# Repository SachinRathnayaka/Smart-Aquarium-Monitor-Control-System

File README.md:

<div align="center">

# 🐠 SRAqua Guard
### Ultimate Smart Aquarium Monitor & Automation System

*Real-time water telemetry · Intelligent automation · Voice control · Cross-platform monitoring*

---

**Author:** [Sachin Rathnayaka](https://github.com/SachinRathnayaka) &nbsp;·&nbsp; **Repo:** [Smart-Aquarium-Monitor-Control-System](https://github.com/SachinRathnayaka/Smart-Aquarium-Monitor-Control-System) &nbsp;·&nbsp; **Live Demo:** [Web Dashboard](https://sachinrathnayaka.github.io/Smart-Aquarium-Monitor-Control-System/)

</div>

---

## 📖 Table of Contents

- [Project Status](#-project-status)
- [Project Overview](#-project-overview)
- [Visual Showcase](#-visual-showcase)
- [Key Features](#-key-features)
- [System Architecture](#-system-architecture)
- [Repository Structure](#-repository-structure)
- [Getting Started](#-getting-started)
  - [Prerequisites](#prerequisites)
  - [1 · Firmware (ESP32)](#1--firmware-esp32)
  - [2 · Web Dashboard](#2--web-dashboard)
  - [3 · Android App](#3--android-app)
  - [4 · Windows Desktop App](#4--windows-desktop-app)
  - [Pre-built Binaries](#pre-built-binaries)
- [Firebase Configuration](#-firebase-configuration)
- [Voice Commands](#-voice-commands)
- [Sensor Calibration](#-sensor-calibration)
- [Troubleshooting](#-troubleshooting)
- [Electrical Safety](#-electrical-safety)
- [Hardware & PCB](#-hardware--pcb)
- [Bill of Materials](#-bill-of-materials-summary)
- [Roadmap](#️-roadmap)
- [Contributing](#-contributing)
- [Licensing](#-licensing)

---

## 🚧 Project Status

**Status: Active Development**

SRAqua Guard is an actively developed open-source hardware and software project. Features, firmware behaviour, PCB revisions, and application interfaces may change between releases. The project is functional and has been tested with real hardware — see the Visual Showcase for screenshots. Always refer to the latest `main` branch for the most current state.

| Component | Status |
|---|---|
| ESP32 Firmware | ✅ Functional |
| Web Dashboard | ✅ Functional |
| Android App | ✅ Functional |
| Windows Desktop App | ✅ Functional |
| KiCad PCB (Hardware) | ✅ Complete |
| Documentation | ✅ Complete |

---

## 🌊 Project Overview

**SRAqua Guard** is a fully open-source, advanced IoT aquarium monitoring and automation system that transforms any aquarium into an intelligently managed ecosystem. The system is built around an **ESP32 microcontroller** with a custom **KiCad PCB**, pushing real-time sensor telemetry to **Firebase Realtime Database**, and surfaced through three client platforms — a browser-based web dashboard, an Android mobile app, and a Windows desktop app.

The firmware is engineered with a **fully non-blocking `millis()` architecture**, a **DS3231 RTC** as the sole time source (ensuring offline-safe automation), and intelligent fallback behavior: the system continues sensing, controlling, and displaying locally even without Wi-Fi. When battery voltage drops below a threshold, the ESP32 enters a **5-minute deep sleep cycle** to preserve power.

> [!NOTE]
> This project includes **240 V AC mains wiring** for the water heater relay. All high-voltage sections must be handled by a qualified person. Use appropriate insulation, cable sleeving, and maintain required creepage clearances at all times.

---

## 🖼️ Visual Showcase

### Web Dashboard

| Overview | Firebase Setup | Theme Settings |
|:---:|:---:|:---:|
|  |  |  |

| 21-Day Sensor Analytics | 21-Day Feed Analytics | Auto Feeder Scheduler |
|:---:|:---:|:---:|
|  |  |  |

| Live Voice Assistant | Voice Commands List | Alerts & History |
|:---:|:---:|:---:|
|  |  |  |

---

### Android Mobile App

| Firebase Setup | Telemetry & Sensors | Header Navigation | Command Center | App Icon |
|:---:|:---:|:---:|:---:|:---:|
|  |  |  |  |  |

---

### Windows Desktop App

| Main Dashboard | Firebase Setup | Theme Settings | Command Center | Desktop Icon |
|:---:|:---:|:---:|:---:|:---:|
|  |  |  |  |  |

---

### Custom KiCad PCB — 3D Renders

**Standard Renders**

| Top | Bottom | Front | Back | Left | Right |
|:---:|:---:|:---:|:---:|:---:|:---:|
|  |  |  |  |  |  |

**Raytraced Renders**

| Top | Bottom | Front | Back | Left | Right |
|:---:|:---:|:---:|:---:|:---:|:---:|
|  |  |  |  |  |  |

---

## ✨ Key Features

### 🔬 Water Quality Telemetry
- **Temperature** via DS18B20 OneWire sensor — with DS18B20 power-on sentinel (85 °C) rejection
- **pH** via analog sensor module — linear calibration with configurable slope/offset
- **TDS (Total Dissolved Solids)** via analog sensor — temperature-compensated formula
- **Turbidity** via analog sensor — quadratic NTU conversion with 20-point Simple Moving Average (SMA) and degradation trend prediction (days to next maintenance)
- Sensor readings every **2 seconds** in non-blocking loop

### ⚙️ Intelligent Automation
| Condition | Automatic Response |
|---|---|
| Temperature > 29 °C | Cooling fan ON |
| Temperature < 25 °C | Water heater ON (with 30-min hard safety cutoff) |
| Turbidity > 35 NTU or TDS > 500 ppm | Submersible pump ON |
| Turbidity > 70 NTU | Alarm buzzer ON |
| pH outside 6.3–8.3 | Alarm buzzer ON |
| TDS > 1200 ppm | Auto water-change sequence (8-min max, 1-hr cooldown) |
| Pump running 2 h+ with high turbidity | Filter-change alert pushed to Firebase + LCD |
| Temperature sensor fault (OOR / 85 °C sentinel) | Heater hard-disabled, buzzer triggered |
| Battery-only inferred (voltage < 11.2 V, no charge trend) | All loads OFF → 5-min deep sleep cycle |

### 💡 ARGB Lighting Day-Cycle (RTC-driven)
| Time | Lighting |
|---|---|
| 06:00 – 09:59 | Sunrise — dim orange / warm yellow |
| 10:00 – 17:59 | Daytime — bright white / light blue |
| 18:00 – 05:59 | Night — calm breathing blue/purple (non-blocking animation) |

### 🎙️ Voice Assistant
- **8 core command groups** (Status · Feed · Pump · Heater · Fan · Lights · Buzzer · Mode) plus Demo Mode test commands, via the **Web Speech API** — no cloud API key required
- Live transcription displayed in the dashboard header (auto-stops after 15 s of silence, or 5 s after the last detected word)
- Voice TTS feedback: browser speaks alert summaries aloud

### 📅 Auto Fish Feeder
- Servo-based feeder FSM (4-state: Idle → Extend → Hold → Return)
- Unlimited scheduled feeds — configurable time, day(s) of week, specific date, and portion count
- Manual one-click feed button on web/local dashboard
- Daily feed counter persisted in browser `localStorage`

### 🔋 Power Telemetry
- 12 V battery voltage via resistor-divider (×4 ratio) on GPIO 33
- Battery percentage from 9.0 V (0%) to 12.6 V (100%)
- Charging inference via 10-point voltage trend (>50 mV rise = charging)
- Solar charging input terminal on PCB (J15)

### 🖥️ Web Dashboard

👉 **[🚀 Try Live Web Dashboard Here](https://sachinrathnayaka.github.io/Smart-Aquarium-Monitor-Control-System/)** *(Fully functional Demo Mode available — no hardware required!)*

- Pure single-file HTML5/CSS3/JavaScript — **zero build step, zero dependencies to install**
- Firebase Realtime Database v10.8.0 SDK — real-time bidirectional sync
- **4 built-in themes:** Ocean · Cyber · Emerald · Sunset + custom hex color picker
- **Demo Mode** — fully functional without any hardware (simulated sensor data)
- 21-day historical analytics charts (Temperature, pH, TDS, Turbidity, Feed count) via Chart.js
- ARGB hex color picker — picks and syncs live `light_color` to Firebase
- RTC time sync — pushes browser clock to ESP32 via Firebase (`/commands/rtc_sync`)
- Alerts & notification history (last 50 events)

---

## 🏗️ System Architecture

```
┌─────────────────────────────────────────────────────────────────────┐
│                        ESP32 (Firmware)                             │
│                                                                     │
│  Sensors ──► readAllSensors() ──► evaluateAutomation()              │
│  DS18B20 · pH · TDS · Turbidity · Battery                           │
│                    │                                                │
│         millis() non-blocking loop (no delay())                     │
│                    │                                                │
│  ┌─────────────────┼─────────────────────────┐                     │
│  │ DS3231 RTC      │ FastLED ARGB   Servo     │                     │
│  │ (offline time)  │ (day cycle)    (feeder)  │                     │
│  └─────────────────┼─────────────────────────┘                     │
│                    │                                                │
│         pushFirebase() every 5 s  ◄──►  Firebase RTDB              │
│         streamCallback()          ◄──►  /controls + /commands       │
│         Local WebServer (port 80) → in-network dashboard            │
└─────────────────────────────────────────────────────────────────────┘
                              │
                  Firebase Realtime Database
                  /devices/aquaSense/
                  ├── sensors/
                  ├── status/
                  ├── controls/
                  ├── commands/
                  └── alerts/
                              │
          ┌───────────────────┼───────────────────┐
          │                   │                   │
   Web Dashboard        Android App         Windows App
   (index.html)     (WebView wrapper)    (Electron shell)
   Any browser      com.wrscn.sraquaguard  com.wrscn.sraquaguard
```

### ESP32 GPIO Pin Map

| Pin | Signal | Direction |
|-----|--------|-----------|
| GPIO 34 | pH Sensor (Analog) | Input |
| GPIO 35 | TDS Sensor (Analog) | Input |
| GPIO 32 | Turbidity Sensor (Analog) | Input |
| GPIO 25 | DS18B20 Temperature (1-Wire) | Input |
| GPIO 33 | BMS / Battery Voltage (Analog) | Input |
| GPIO 26 | Cooling Fan Relay | Output |
| GPIO 27 | Submersible Pump Relay | Output |
| GPIO 17 | Water Heater Relay ⚠️ 240 V | Output |
| GPIO 23 | Fish Feeder Servo (PWM) | Output |
| GPIO 16 | ARGB LED Strip (WS2812B) | Output |
| GPIO 13 | Alarm Buzzer | Output |
| GPIO 21 | I²C SDA (LCD + RTC) | I²C |
| GPIO 22 | I²C SCL (LCD + RTC) | I²C |
| GPIO 4 | Wi-Fi / Firebase Status LED | Output |

### Arduino Libraries Required

| Library | Purpose | Install via |
|---------|---------|-------------|
| `Firebase ESP Client` by mobizt | Firebase RTDB | Arduino Library Manager |
| `LiquidCrystal I2C` | 16×2 LCD display | Arduino Library Manager |
| `DallasTemperature` | DS18B20 sensor | Arduino Library Manager |
| `OneWire` | 1-Wire bus | Arduino Library Manager |
| `RTClib` | DS3231 RTC | Arduino Library Manager |
| `FastLED` | WS2812B ARGB LEDs | Arduino Library Manager |
| `ESP32Servo` | Servo motor control | Arduino Library Manager |

---

## 📁 Repository Structure

```
Smart-Aquarium-Monitor-Control-System/
│
├── 📁 Firmware/
│   └── ESP32/
│       └── IoT_Based_Smart_Aquarium_Monitor__Control_System_ESP32/
│           ├── IoT_Based_Smart_Aquarium_Monitor__Control_System_ESP32.ino
│           │   # Main ESP32 firmware — non-blocking millis() architecture,
│           │   # offline-safe automation, DS3231 RTC, Firebase RTDB streaming,
│           │   # ARGB day cycle, feeder FSM, battery telemetry, deep sleep
│           └── secrets.example.h
│               # Credential template — copy to secrets.h, fill in values,
│               # add secrets.h to .gitignore (never commit real credentials)
│
├── 📁 Web_Dashboard/
│   ├── index.html          # Single-file dashboard — no build step required
│   └── assets/
│       └── logo.png
│
├── 📁 Android_App/          # Android Studio project (com.wrscn.sraquaguard)
│   ├── app/
│   │   ├── build.gradle    # compileSdk 35, minSdk 23 (Android 6.0+), versionName 1.0
│   │   └── src/main/
│   │       ├── AndroidManifest.xml
│   │       ├── assets/
│   │       │   ├── index.html      # Bundled web dashboard
│   │       │   └── assets/logo.png
│   │       ├── java/com/wrscn/sraquaguard/
│   │       │   └── MainActivity.java  # WebView with immersive fullscreen
│   │       └── res/
│   │           ├── drawable/sraqua_logo.png
│   │           ├── mipmap-*/       # Launcher icons (all densities)
│   │           └── values/
│   │               ├── colors.xml
│   │               └── styles.xml  # Theme.SRAquaGuard (dark slate)
│   └── README.md
│
├── 📁 Windows_App/          # Electron desktop application
│   ├── main.js             # BrowserWindow 1280×800, contextIsolation: true
│   ├── index.html          # Dashboard file loaded by Electron
│   ├── package.json        # electron + electron-builder, NSIS target
│   ├── package-lock.json
│   └── assets/
│       ├── logo.ico        # Windows app icon
│       └── logo.png
│
├── 📁 Hardware/             # KiCad 10.0.3 PCB project
│   ├── *.kicad_pcb         # PCB layout
│   ├── *.kicad_sch         # Schematic
│   ├── *.kicad_pro         # Project file
│   ├── 3D_Models/
│   │   ├── 3D_Standard/    # 6 standard 3D renders (Top/Bottom/Sides)
│   │   └── 3D_Raytraced/   # 6 raytraced 3D renders (Top/Bottom/Sides)
│   ├── Gerber_Files/       # Full Gerber set (F_Cu, B_Cu, Masks, Silkscreen,
│   │   ├── *.gbr           #   Edge Cuts, Drill files) + zipped Gerber bundle
│   │   └── Gerber_ZIP/
│   └── DIY_Etching_PDFs/   # PDFs for DIY toner-transfer / UV etching
│       ├── Copper_Layers/  # Top + Bottom copper (normal + mirrored)
│       ├── Silkscreen_Layers/
│       └── Assembly_Drawings/
│
├── 📁 Docs/
│   ├── Bill_of_Materials.md          # 41 line items · 74 total components
│   ├── Components_List_BOM.csv       # Machine-readable BOM
│   ├── Schematic_Diagram.pdf         # Full schematic PDF export
│   └── PCB_Artwork_Etching_Layout.pdf
│
├── 📁 Images/               # All screenshots and renders used in this README
│   ├── 3D_PCB_Isometric.png
│   ├── ESP32_Pin_Pitch_Dimensions.png
│   ├── Web_Dashboard_Screenshots/    # 9 screenshots
│   ├── Mobile_App_Screenshots/       # 5 screenshots
│   └── Desktop_App_Screenshots/      # 5 screenshots
│
└── README.md
```

---

## 🚀 Getting Started

### Prerequisites

| Requirement | Details |
|---|---|
| Arduino IDE ≥ 2.x **or** PlatformIO | For flashing the ESP32 firmware |
| ESP32 Arduino Core | Board package for ESP32 (add `https://raw.githubusercontent.com/espressif/arduino-esp32/gh-pages/package_esp32_index.json` to board manager) |
| Firebase project | Free Spark plan is sufficient — Realtime Database enabled |
| Any modern browser | Chrome recommended for Voice Control (Web Speech API) |
| Android Studio (optional) | To build the `.apk` from source |
| Node.js ≥ 18 (optional) | To run/build the Windows Electron app from source |

---

### 1 · Firmware (ESP32)

#### Step 1 — Install Libraries

Open **Arduino IDE → Tools → Manage Libraries** and install each of the following:

```
Firebase ESP Client    (by mobizt)
LiquidCrystal I2C
DallasTemperature
OneWire
RTClib
FastLED
ESP32Servo
```

#### Step 2 — Configure Credentials (secrets.h pattern)

To avoid accidentally committing credentials to a public repository, use the recommended `secrets.h` approach:

**2a.** Copy the provided template:
```
Firmware/ESP32/.../secrets.example.h  →  copy as  secrets.h
```

**2b.** Open `secrets.h` and fill in your values:
```cpp
// secrets.h — DO NOT commit this file
#pragma once

// Wi-Fi
#define WIFI_SSID     "YOUR_WIFI_SSID"
#define WIFI_PASSWORD "YOUR_WIFI_PASSWORD"

// Firebase
#define API_KEY       "YOUR_FIREBASE_API_KEY"
#define DATABASE_URL  "YOUR_FIREBASE_DATABASE_URL"
#define USER_EMAIL    "YOUR_FIREBASE_USER_EMAIL"
#define USER_PASSWORD "YOUR_FIREBASE_USER_PASSWORD"
```

**2c.** Add `secrets.h` to your `.gitignore` so it is never tracked:
```
# .gitignore
secrets.h
```

The main `.ino` file already contains `#include "secrets.h"` and uses these defines — **do not paste real credentials directly into the `.ino` file.**

> [!WARNING]
> **Never commit real credentials to a public repository.** The `secrets.example.h` template uses intentionally non-functional placeholder strings. Always work from `secrets.h` (git-ignored) in your local copy.

> [!NOTE]
> **Firebase API Key vs secret credentials:** The Firebase Web API Key (found in Project Settings) is a *project identifier* — it is not a secret by itself, as it is embedded in every web client. What must be protected are your **Firebase Auth user email and password** (the device account). Firebase Database Rules (see the Firebase Configuration section) are your primary security boundary — ensure they are correctly configured before going live.

#### Step 3 — Sensor Calibration (optional)

The firmware ships with **Dummy Data switches** that generate realistic random values for dry testing without any sensors connected:

```cpp
bool DUMMY_PH        = false;   // set true for dry test
bool DUMMY_TDS       = false;
bool DUMMY_TURBIDITY = false;
bool DUMMY_TEMP      = false;
bool DUMMY_BATTERY   = false;
```

For a real deployment, calibrate your pH probe and update:

```cpp
float PH_SLOPE  = -5.70f;   // Adjust after 2-point calibration
float PH_OFFSET = 21.34f;
```

#### Step 4 — Flash

Select **Board: `ESP32 Dev Module`**, choose the correct COM port, then click **Upload**.

---

### 2 · Web Dashboard

The dashboard is a **single self-contained HTML file** with no build step.

**Option A — Open locally in browser**
```
Open Web_Dashboard/index.html directly in Chrome or Edge
```

**Option B — Host on GitHub Pages**
1. Copy `Web_Dashboard/index.html` and `Web_Dashboard/assets/` to the root of a GitHub Pages branch.
2. Enable GitHub Pages in your repository settings.
3. Share the `https://<username>.github.io/<repo>/` URL.

**Connecting to Firebase**

When the dashboard loads, a setup modal appears. Enter your Firebase project credentials:

| Field | Where to find it |
|---|---|
| **API Key** | Firebase Console → Project Settings → General |
| **Database URL** | Firebase Console → Realtime Database → Data tab |
| **User Email** | Firebase Console → Authentication → Users |
| **User Password** | The password for that Firebase Auth user |

Click **Connect Firebase** to go live, or **Enter Demo Mode** to explore with simulated data — no hardware needed.

---

### 3 · Android App

**Build from source (Android Studio)**

1. Open the `Android_App/` folder in **Android Studio**.
2. Allow Gradle to sync (compileSdk 35, minSdk 23 — Android 6.0+).
3. Build the APK:

```bash
./gradlew assembleDebug
# Output: Android_App/app/build/outputs/apk/debug/app-debug.apk
```

Or use **Build → Build App Bundle(s)/APK(s) → Build APK(s)** from the menu.

The app loads `index.html` bundled in `app/src/main/assets/` via a hardware-accelerated WebView with immersive fullscreen mode. Firebase credentials are configured through the in-app setup modal — no separate `google-services.json` is needed.

> [!NOTE]
> The web dashboard inside the APK includes its own Firebase setup flow. Simply enter your Firebase credentials the first time you launch the app, and they are persisted in the WebView's `localStorage`.

---

### 4 · Windows Desktop App

**Run from source**

```bash
cd Windows_App
npm install
npm start
```

**Build an installable `.exe`**

```bash
npm run build
# Output: Windows_App/dist/SRAqua Guard Setup x.x.x.exe  (NSIS installer)
```

The Electron window opens at **1280 × 800** (minimum 1000 × 650) and loads `index.html`. Node integration is disabled (`nodeIntegration: false`, `contextIsolation: true`) for security.

---

### Pre-built Binaries

Pre-compiled binaries are published through the **GitHub Releases** page. Check the Releases tab for the latest available versions:

| Platform | File | Notes |
|---|---|---|
| Android | `SRAqua_Guard_v1.0.apk` | Sideload — enable "Install from unknown sources" in device settings |
| Windows | `SRAqua Guard Setup 1.0.0.exe` | NSIS installer — run and follow on-screen prompts |

👉 **[View GitHub Releases](https://github.com/SachinRathnayaka/Smart-Aquarium-Monitor-Control-System/releases)**

> [!NOTE]
> If no release is listed yet, build from source using the instructions above — it only takes a few minutes.

---

## 🔥 Firebase Configuration

### Database Path Structure

All device data lives under a single root path:

```
/devices/aquaSense/
├── sensors/            ← pushed by ESP32 every 5 s
│   ├── temperature_c
│   ├── ph_value / ph_voltage
│   ├── tds_ppm / tds_voltage
│   ├── turbidity_ntu / turbidity_sma
│   ├── predicted_days_to_maintenance
│   ├── battery_voltage / battery_percent
│   ├── charging_inferred
│   ├── dummy_ph / dummy_tds / dummy_turbidity / dummy_temp / dummy_battery
│   └── timestamp
├── status/             ← pushed by ESP32 every 5 s
│   ├── manual_mode / fan / pump / heater / buzzer
│   ├── water_change_active / filter_change_required
│   ├── wifi_connected / firebase_ready / battery_only_mode
├── controls/           ← written by dashboard, read by ESP32 stream
│   ├── manual_mode / manual_fan / manual_pump
│   ├── manual_heater / manual_buzzer
│   ├── manual_light / light_color
│   └── feed_now
├── commands/           ← one-shot voice hooks (auto-reset after each push)
│   ├── voice_feed
│   ├── voice_pump
│   └── rtc_sync
└── alerts/
    └── filter_change_required_at
```

### Recommended Security Rules

The rules below apply **least-privilege** access: only authenticated users can read or write device data. No unauthenticated access is permitted at any path.

```json
{
  "rules": {
    ".read":  false,
    ".write": false,
    "devices": {
      "aquaSense": {
        "sensors":  { ".read": "auth != null", ".write": "auth != null" },
        "status":   { ".read": "auth != null", ".write": "auth != null" },
        "controls": { ".read": "auth != null", ".write": "auth != null" },
        "commands": { ".read": "auth != null", ".write": "auth != null" },
        "alerts":   { ".read": "auth != null", ".write": "auth != null" }
      }
    }
  }
}
```

> [!IMPORTANT]
> **Never use `".read": true, ".write": true`** (open rules) — this exposes your device data to anyone on the internet. The root-level `false` defaults above ensure that any path not explicitly listed is denied by default. The firmware authenticates using the dedicated Firebase Auth device account configured in `secrets.h`.

> [!NOTE]
> For a single-owner deployment, the `auth != null` check is sufficient since only your device account and your own dashboard sessions are authenticated. For multi-user or team setups, consider tightening rules further using `auth.uid` matching against an allow-list stored in the database.

> [!TIP]
> **Future enhancement — role-based rules:** In an ideal setup, write permissions would be further restricted by path role: `sensors/` and `status/` would be write-restricted to the ESP32 device account only, while `controls/` and `commands/` would be writable by dashboard users. This can be implemented by storing your ESP32's Firebase Auth UID in the database and matching against it in rules. For a personal single-device deployment the current rules are adequate.

### Authentication Setup

1. In Firebase Console → **Authentication → Sign-in method**, enable **Email/Password**.
2. Under **Authentication → Users**, click **Add user** and create a dedicated device account.
3. Use those credentials in the firmware's `USER_EMAIL` and `USER_PASSWORD` defines.

---

## 🎙️ Voice Commands

Voice control uses the browser's built-in **Web Speech API** (no API key required). Click the **Voice Control** button in the dashboard header, then speak any of the following commands:

| Voice Command | Alternatives | Action |
|---|---|---|
| **"Tell Status"** | "Tank Status", "How is the water" | Reads the current sensor values via TTS and reports whether the aquarium conditions are healthy or critical |
| **"Feed"** | — | Triggers fish feeder immediately — sends `voice_feed` to Firebase |
| **"Pump on"** | "Turn on pump" | Enables manual mode and turns pump ON — sends `voice_pump` to Firebase |
| **"Pump off"** | "Turn off pump" | Enables manual mode and turns pump OFF |
| **"Heater on"** | "Turn on heater" | Enables manual mode and turns heater ON |
| **"Heater off"** | "Turn off heater" | Enables manual mode and turns heater OFF |
| **"Fan on"** | "Turn on fan" | Enables manual mode and turns cooling fan ON |
| **"Fan off"** | "Turn off fan" | Enables manual mode and turns cooling fan OFF |
| **"Lights on"** | "Light on", "Turn on lights" | Turns ARGB tank lights ON |
| **"Lights off"** | "Light off", "Turn off lights" | Turns ARGB tank lights OFF |
| **"Buzzer on"** | "Turn on buzzer" | Manually enables alarm buzzer |
| **"Buzzer off"** | "Turn off buzzer" | Manually disables alarm buzzer |
| **"Auto Mode"** | "Auto" | Switches system to automatic control |
| **"Manual Mode"** | "Manual" | Switches system to manual control |
| **"Test Alert"** | — | Simulates a critical alert (Demo Mode) |
| **"Fix Alert"** | "Reset Alert" | Restores simulated normal conditions (Demo Mode) |

> [!NOTE]
> Voice control requires a browser that supports the Web Speech API (Chrome and Edge recommended). Microphone permission must be granted. The recognition session auto-stops after **15 seconds** of silence, or **5 seconds** after the last detected word. Web Speech API support and behaviour may vary by browser version and operating system — Chrome on desktop provides the most consistent experience.

---

## 🧪 Sensor Calibration

The firmware ships with **Dummy Data mode** for all sensors — ideal for testing the dashboard and Firebase integration without any physical hardware connected. Set the relevant flag to `true` in the firmware:

```cpp
bool DUMMY_PH        = false;   // set true to generate simulated pH readings
bool DUMMY_TDS       = false;
bool DUMMY_TURBIDITY = false;
bool DUMMY_TEMP      = false;
bool DUMMY_BATTERY   = false;
```

### pH Calibration (2-point method)

Perform a standard 2-point calibration using pH 4.0 and pH 7.0 buffer solutions:

1. Dip the probe in **pH 7.0** buffer → note the raw ADC voltage reading from the serial monitor.
2. Dip the probe in **pH 4.0** buffer → note the second ADC voltage reading.
3. Calculate slope and offset from those two readings, then update the firmware:

```cpp
float PH_SLOPE  = -5.70f;   // Volts per pH unit — adjust after calibration
float PH_OFFSET = 21.34f;   // Intercept — adjust after calibration
```

> [!NOTE]
> The default values above (`PH_SLOPE = -5.70`, `PH_OFFSET = 21.34`) are example starting points. Your actual probe will require calibration — results will be inaccurate if you skip this step.

### TDS Calibration

The TDS sensor uses a temperature-compensated formula built into the firmware. For best accuracy, perform the reading in water at a known temperature and compare against a reference TDS meter. Adjust the conversion coefficient in firmware if needed.

### Turbidity Calibration

Turbidity uses a quadratic NTU conversion with a 20-point Simple Moving Average (SMA) for stability. The SMA also drives the degradation trend prediction (days to next filter maintenance). If your sensor module outputs a different voltage curve, update the quadratic coefficients in the firmware.

### Battery Voltage Calibration

The battery voltage is measured via a ×4 resistor divider on GPIO 33. If your resistor values differ slightly, adjust the divider ratio constant in firmware to match your measured real-world voltage.

---

## 🛠️ Troubleshooting

| Symptom | Likely Cause | Fix |
|---|---|---|
| ESP32 won't connect to Wi-Fi | Wrong credentials in `secrets.h` | Double-check `WIFI_SSID` and `WIFI_PASSWORD` — no extra spaces |
| Firebase stream not receiving data | Firebase rules blocking access | Verify security rules and that `USER_EMAIL`/`USER_PASSWORD` match an active Auth user |
| No sensor readings on dashboard | Wiring issue or Dummy Data off | Check GPIO connections against the pin map, or enable Dummy Data mode for testing |
| Temperature always reads 85 °C | DS18B20 power-on sentinel not rejected / wiring fault | Check 1-Wire pull-up resistor (4.7 kΩ on GPIO 25) and sensor wiring |
| pH / TDS / Turbidity readings wildly wrong | Uncalibrated sensor | Perform 2-point calibration — see Sensor Calibration section above |
| Android build fails (Gradle error) | Gradle/SDK mismatch | Run **File → Sync Project with Gradle Files** in Android Studio; ensure SDK 35 is installed |
| Electron app won't start | Missing Node modules | Run `npm install` inside `Windows_App/` before `npm start` |
| Voice commands not recognised | Browser or permission issue | Use Chrome or Edge; grant microphone permission when prompted; ensure Web Speech API is supported on your OS |
| ARGB lights show wrong colour | `light_color` hex not synced | Use the colour picker in the dashboard — it pushes the hex directly to Firebase `/controls/light_color` |
| Heater relay not triggering | Heater hard-disabled due to sensor fault | Check serial monitor for fault messages; verify DS18B20 wiring and that temperature reads correctly |

> [!NOTE]
> For firmware issues, always open the **Arduino IDE Serial Monitor** at **115200 baud** immediately after flashing — the firmware prints detailed startup diagnostics and runtime status every cycle.

---

## ⚡ Electrical Safety

> [!CAUTION]
> **This project involves 240 V AC mains voltage. Incorrect wiring can cause electric shock, fire, or death. Read this section fully before building.**

| Safety Requirement | Details |
|---|---|
| **Qualified person** | All mains-voltage wiring (relay K5, terminals J17/J18) must be connected and tested only by a suitably qualified person |
| **Mains-rated wiring** | Use cable rated ≥ 250 V for all AC sections — correctly sleeved and terminated |
| **Fusing** | Two 5 A / 250 V slow-blow fuses are included in the BOM and PCB layout — always fit them before energising |
| **Enclosure** | House the PCB in an IP-rated enclosure appropriate for the installation environment. Never leave mains terminals exposed |
| **Creepage & clearance** | Maintain the required PCB creepage distances between high-voltage and low-voltage traces — do not bridge them with solder bridges or conductive debris |
| **Low/high voltage separation** | Keep all 240 V AC wiring physically separated from the 5 V / 3.3 V signal wiring at all times |
| **RCD / GFCI protection** | Install an RCD (residual current device) or GFCI on the mains circuit feeding this system — especially important near water |
| **Waterproofing** | The PCB is not waterproof. Protect it from splashes. All sensor probes that enter the aquarium must be rated for submersion |
| **Heater safety cutoff** | The firmware enforces a **30-minute hard cutoff** on the heater relay and disables it on any temperature sensor fault — do not bypass this logic |

**Never power the mains section of the board during firmware development or debugging.** Work with the AC terminals disconnected and use the Dummy Data mode for testing.

---

## 🔩 Hardware & PCB

The custom PCB was designed in **KiCad 10.0.3** as a through-hole friendly layout suitable for DIY etching or professional PCB fabrication.

### PCB Outputs Provided

| Output | Location | Use |
|---|---|---|
| KiCad project files (`.kicad_pcb`, `.kicad_sch`, `.kicad_pro`) | `Hardware/` | Edit in KiCad 10.x |
| Gerber files + drill files | `Hardware/Gerber_Files/` | Send to any PCB fab (JLCPCB, PCBWay, OSH Park…) |
| Zipped Gerber bundle | `Hardware/Gerber_Files/Gerber_ZIP/` | Ready to upload directly to fab ordering page |
| DIY etching PDFs | `Hardware/DIY_Etching_PDFs/` | Toner-transfer / photoresist etching |
| Standard 3D renders (×6) | `Hardware/3D_Models/3D_Standard/` | Documentation / review |
| Raytraced 3D renders (×6) | `Hardware/3D_Models/3D_Raytraced/` | Realistic visual preview |
| Schematic PDF | `Docs/Schematic_Diagram.pdf` | Reference during assembly |

### ESP32 Fit Note

The PCB accepts a standard **ESP32-WROOM-32 / ESP32-DevKitC 38-pin** module mounted on two 1×19 female pin socket rows.

> [!WARNING]
> The board routes **240 V AC mains** through relay K5 (water heater output). Terminals J17 (AC out) and J18 (AC in) must use mains-rated wiring (≥ 250 V rated, properly sleeved). Observe required creepage distances. This section must only be connected and tested by a qualified person.

---

## 📋 Bill of Materials Summary

Full BOM: [`Docs/Bill_of_Materials.md`](Docs/Bill_of_Materials.md) · CSV: [`Docs/Components_List_BOM.csv`](Docs/Components_List_BOM.csv)

**The hardware design uses exclusively through-hole components to support DIY-friendly assembly.**

| Category | Key Parts |
|---|---|
| Microcontroller | ESP32-WROOM-32 / DevKitC (38-pin) |
| Transistors | BC547 NPN (relay drivers) |
| Relays | SANYOU SRD Form-C (5 V coil, 10 A / 250 VAC) |
| Diodes | SR560 Schottky (4×) · 1N4007 rectifier (4×) · RS505 bridge (1×) | 
| Capacitors | 100 nF ceramic (4×) · 470 µF electrolytic (1×) · 1000 µF (3×) · 10 µF (1×) |
| Resistors | 330 Ω – 30 kΩ (various, ¼ W 5%) |
| Fuses | 5 A / 250 V slow-blow, 5×20 mm |
| Power Module | LM2596 / MP1584 DC-DC buck (12 V → 5 V) |
| Connectors | Screw terminals (5.08 mm) + pin headers (2.54 mm) |
| Switch | 6×6 mm tactile push button (Reset/Boot) |

---

## 🗺️ Roadmap

Planned improvements and ideas for future releases. Community contributions towards any of these are very welcome — see [Contributing](#-contributing).

| Feature | Description | Status |
|---|---|---|
| OTA firmware updates | Push firmware updates to the ESP32 wirelessly via Firebase or a local server | Planned |
| Additional sensor support | Water level sensor, dissolved oxygen (DO), CO₂ | Planned |
| Push notifications | Mobile push alerts via Firebase Cloud Messaging when alarms trigger | Planned |
| Advanced automation rules | User-configurable threshold values stored in Firebase (no reflash required) | Planned |
| Extended analytics | Analytics beyond 21 days; CSV export of historical sensor data | Planned |
| Multi-aquarium support | Extend the Firebase path structure to manage multiple tanks from one dashboard | Planned |
| Role-based Firebase security | Per-path UID-restricted rules (ESP32 write-only to `sensors/status/`, dashboard write-only to `controls/commands/`) | Planned |
| Android: native push notifications | Background service for alarm delivery when the app is not in the foreground | Planned |

> [!NOTE]
> This roadmap reflects current intentions and may change. Items marked **Planned** have not been started. If you have ideas or want to contribute to any of these, open an issue to discuss.

---

## 🤝 Contributing

Contributions are warmly welcomed! Whether it's a bug fix, new feature, improved calibration formula, or documentation update — please feel free to open an issue or pull request.

**Guidelines:**

1. **Fork** the repository and create your branch from `main`.
2. Follow the existing code style — especially the non-blocking `millis()` pattern in firmware (no `delay()` in `loop()`).
3. For dashboard changes, test in both **Demo Mode** and **Firebase Mode**.
4. For hardware changes, verify in KiCad 10.x and update the BOM accordingly.
5. **Never commit real Wi-Fi SSIDs, passwords, or Firebase API keys** — always use placeholder strings.
6. Open a **Pull Request** with a clear description of what was changed and why.

**Reporting Issues:**

Please include your ESP32 core version, Arduino IDE version, and relevant serial output when reporting firmware bugs.

---

## 📜 Licensing

This project utilizes a multi-licensing model to cover software, hardware, and documentation appropriately:

- 💻 **Software & Firmware:** Licensed under the [MIT License](LICENSE) (ESP32 Firmware, Web Dashboard, Android & Windows Apps).
- 🛠️ **Hardware Design:** Licensed under the [CERN-OHL-S-2.0](LICENSE-HARDWARE) (KiCad Schematics & PCB Layouts).
- 📄 **Documentation & Media:** Licensed under [CC BY 4.0](LICENSE-DOCS) (Guides, Images, and Diagrams).

Copyright © 2026 Sachin Rathnayaka (WRSCN)

---

<div align="center">

Made with ❤️ by **[Sachin Rathnayaka (WRSCN)](https://github.com/SachinRathnayaka)**

⭐ If this project helped you, please consider giving it a star on GitHub!

</div>

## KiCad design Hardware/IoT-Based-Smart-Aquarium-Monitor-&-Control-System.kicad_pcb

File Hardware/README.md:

# Hardware Architecture & KiCad PCB Design

This directory contains the KiCad 10.0 schematic and PCB layout files for the SRAqua Guard Smart Aquarium Automation System.

## License
All hardware schematics, PCB designs, and 3D models in this directory are licensed under the **CERN Open Hardware Licence Version 2 - Strongly Reciprocal (CERN-OHL-S-2.0)**.

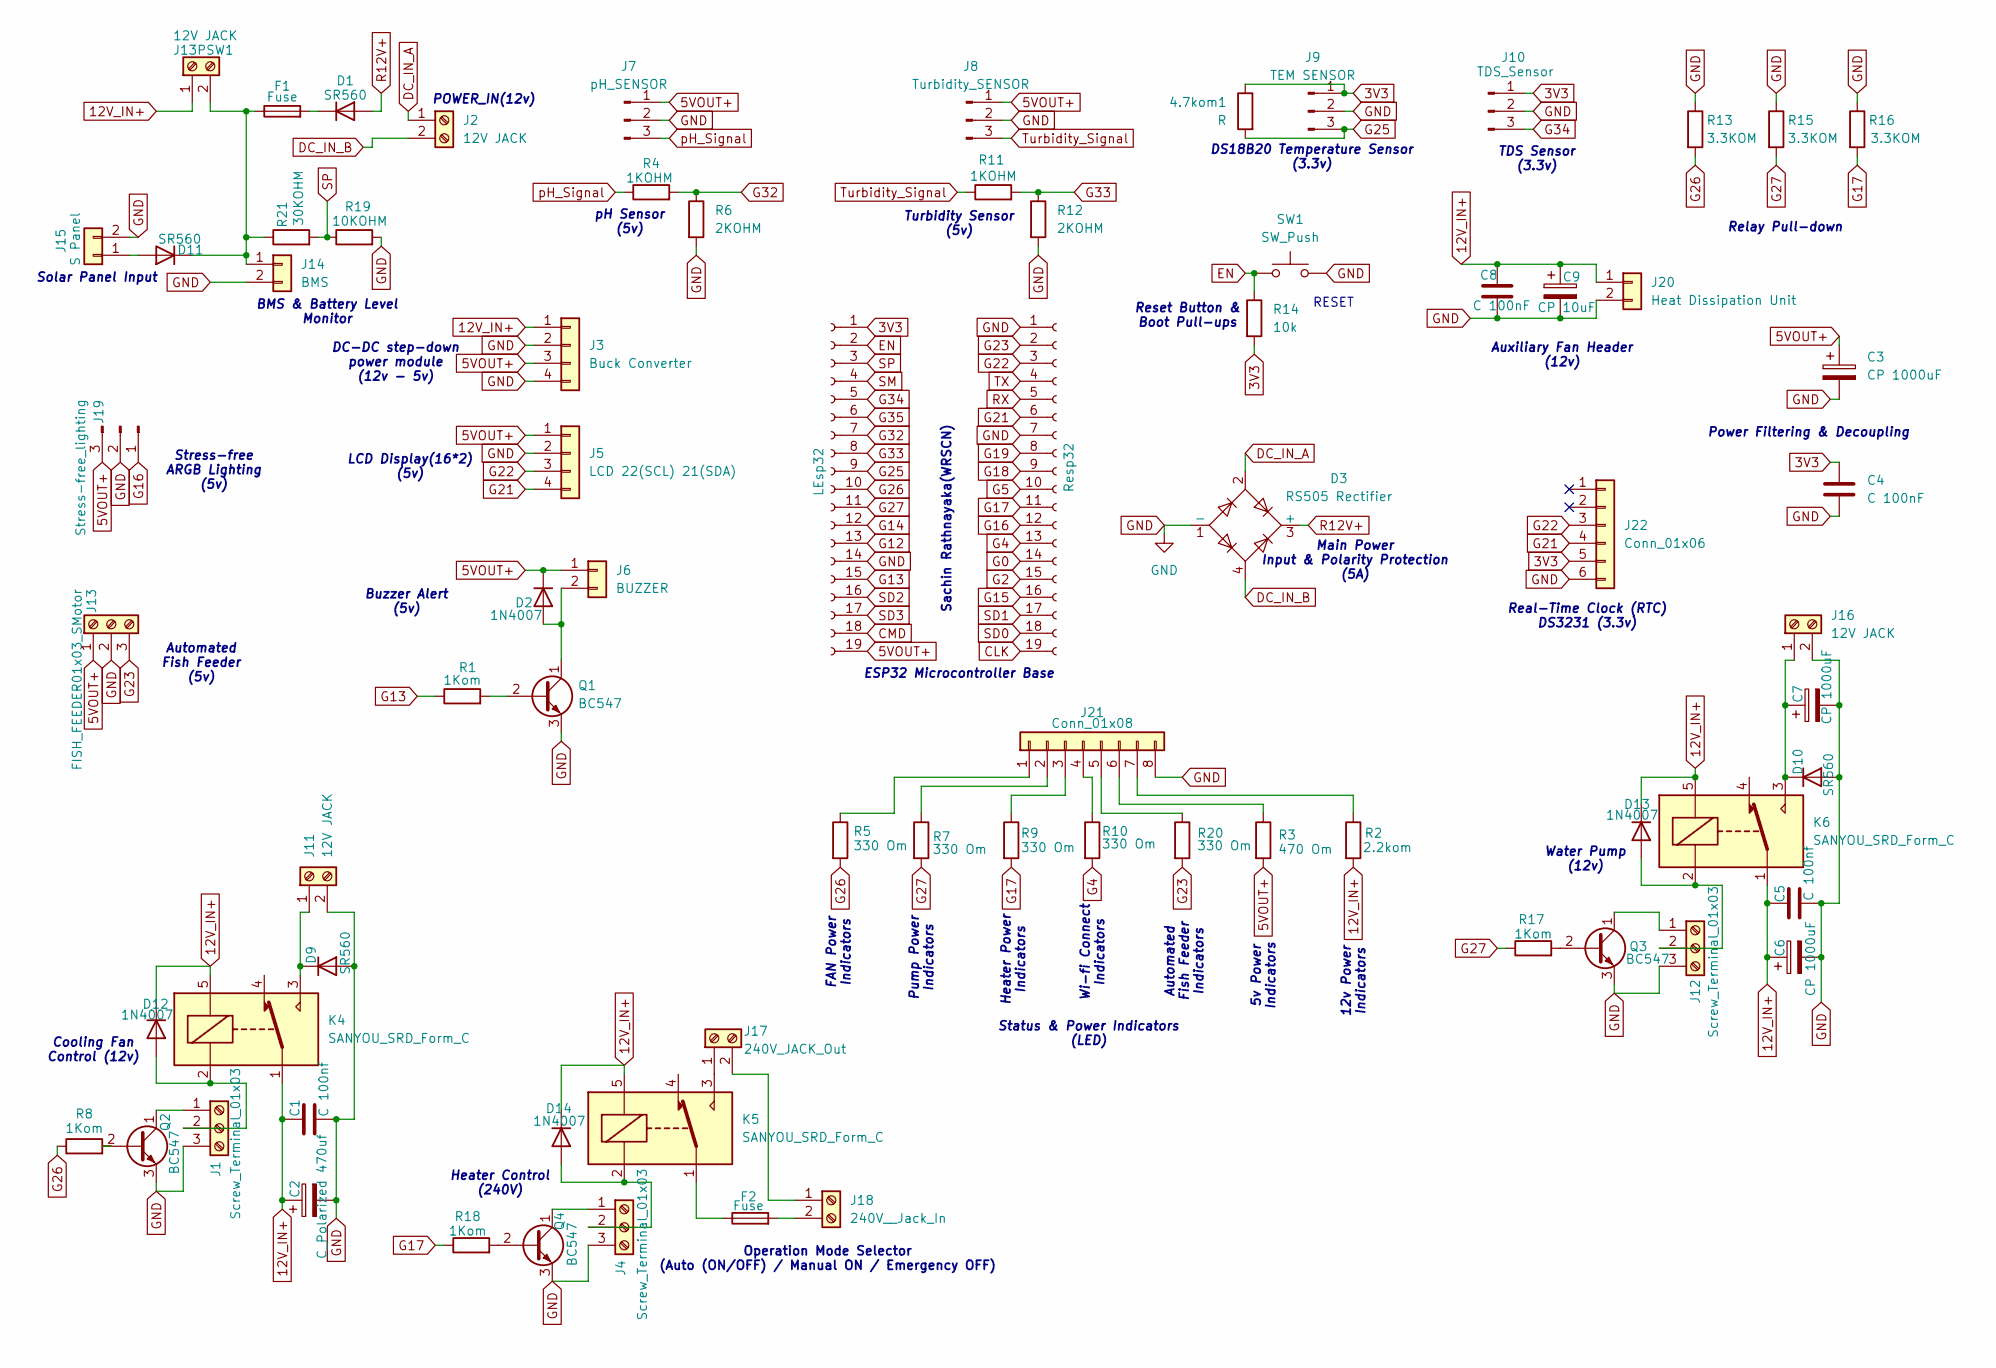
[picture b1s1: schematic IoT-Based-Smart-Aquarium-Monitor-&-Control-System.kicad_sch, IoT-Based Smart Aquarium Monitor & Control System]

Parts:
4.7kom1: R; R_Axial_DIN0207_L6.3mm_D2.5mm_P10.16mm_Horizontal
C1, C5: C 100nf; CP_Radial_D8.0mm_P3.50mm
C2: C_Polarized 470uf; C_Disc_D5.0mm_W2.5mm_P5.00mm
C3, C6, C7: CP 1000uF; CP_Radial_D10.0mm_P5.00mm
C4, C8: C 100nF; C_Disc_D5.0mm_W2.5mm_P5.00mm
C9: CP 10uF; CP_Radial_D5.0mm_P2.00mm
D1, D9, D10, D11: SR560; D_DO-41_SOD81_P10.16mm_Horizontal
D2, D12, D13, D14: 1N4007; D_DO-41_SOD81_P10.16mm_Horizontal
D3: RS505 Rectifier; Diode_Bridge_19.0x3.5x10.0mm_P5.0mm
F1, F2: Fuse; Fuseholder_Cylinder-5x20mm_Schurter_0031_8201_Horizontal_Op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
J1, J4, J12: Screw_Terminal_01x03; TerminalBlock_Phoenix_MKDS-1,5-3-5.08_1x03_P5.08mm_Horizont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
J2, J11, J13PSW1, J16: 12V JACK; TerminalBlock_Phoenix_MKDS-1,5-2-5.08_1x02_P5.08mm_Horizont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
J3: Buck Converter; PinHeader_1x04_P2.54mm_Vertical
J5: LCD 22(SCL) 21(SDA); PinHeader_1x04_P2.54mm_Vertical
J6: BUZZER; PinHeader_1x02_P2.54mm_Vertical
J7: pH_SENSOR; PinHeader_1x03_P2.54mm_Vertical
J8: Turbidity_SENSOR; PinHeader_1x03_P2.54mm_Vertical
J9: TEM SENSOR; PinHeader_1x03_P2.54mm_Vertical
J10: TDS_Sensor; PinHeader_1x03_P2.54mm_Vertical
J13: FISH_FEEDER01x03_SMotor; TerminalBlock_Phoenix_MKDS-1,5-3-5.08_1x03_P5.08mm_Horizont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
J14: BMS; TerminalBlock_Phoenix_MKDS-1,5-2-5.08_1x02_P5.08mm_Horizont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
J15: S Panel; TerminalBlock_Phoenix_MKDS-1,5-2-5.08_1x02_P5.08mm_Horizont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
J17: 240V_JACK_Out; TerminalBlock_Phoenix_MKDS-1,5-2-5.08_1x02_P5.08mm_Horizont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
J18: 240V__Jack_In; TerminalBlock_Phoenix_MKDS-1,5-2-5.08_1x02_P5.08mm_Horizont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
J19: Stress-free_lighting; PinHeader_1x03_P2.54mm_Vertical
J20: Heat Dissipation Unit; PinHeader_1x02_P2.54mm_Vertical
J21: Conn_01x08; PinHeader_1x08_P2.54mm_Vertical
J22: Conn_01x06; PinSocket_1x06_P2.54mm_Vertical
K4, K5, K6: SANYOU_SRD_Form_C; Relay_SPDT_SANYOU_SRD_Series_Form_C
LEsp32: PinSocket_1x19_P2.54mm_Vertical
Q1, Q2, Q3, Q4: BC547; TO-92_Inline
R1, R8, R17, R18: 1Kom; R_Axial_DIN0207_L6.3mm_D2.5mm_P10.16mm_Horizontal
R2: 2.2kom; R_Axial_DIN0207_L6.3mm_D2.5mm_P10.16mm_Horizontal
R3: 470 Om; R_Axial_DIN0207_L6.3mm_D2.5mm_P10.16mm_Horizontal
R4, R11: 1KOHM; R_Axial_DIN0207_L6.3mm_D2.5mm_P10.16mm_Horizontal
R5, R7, R9, R10, R20: 330 Om; R_Axial_DIN0207_L6.3mm_D2.5mm_P10.16mm_Horizontal
R6, R12: 2KOHM; R_Axial_DIN0207_L6.3mm_D2.5mm_P10.16mm_Horizontal
R13, R15, R16: 3.3KOM; R_Axial_DIN0207_L6.3mm_D2.5mm_P10.16mm_Horizontal
R14: 10k; R_Axial_DIN0207_L6.3mm_D2.5mm_P10.16mm_Horizontal
R19: 10KOHM; R_Axial_DIN0207_L6.3mm_D2.5mm_P10.16mm_Horizontal
R21: 30KOHM; R_Axial_DIN0207_L6.3mm_D2.5mm_P10.16mm_Horizontal
Resp32: PinSocket_1x19_P2.54mm_Vertical
SW1: SW_Push; SW_PUSH_6mm

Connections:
3V3: 4.7kom1.1, C4.1, J9.1, J10.1, J22.5, LEsp32.1, R14.2
5VOUT+: C3.1, D2.1 (K), J3.3, J5.1, J6.1, J7.1, J8.1, J13.1, J19.3, LEsp32.19, R3.2
12V_IN+: C1.1, C2.1, C5.1, C6.1, C8.1, C9.1, D12.1 (K), D13.1 (K), D14.1 (K), J3.1, J13PSW1.1, J20.1, K4.1, K4.5, K5.5, K6.1, K6.5, R2.2
CLK: Resp32.19
CMD: LEsp32.18
DC_IN_A: D3.2, J2.1
DC_IN_B: D3.4, J2.2
EN: LEsp32.2, R14.1, SW1.1
G0: Resp32.14
G2: Resp32.15
G4: R10.2, Resp32.13
G5: Resp32.10
G12: LEsp32.13
G13: LEsp32.15, R1.1
G14: LEsp32.12
G15: Resp32.16
G16: J19.1, Resp32.12
G17: R9.2, R16.2, R18.1, Resp32.11
G18: Resp32.9
G19: Resp32.8
G21: J5.4, J22.4, Resp32.6
G22: J5.3, J22.3, Resp32.3
G23: J13.3, R20.2, Resp32.2
G25: 4.7kom1.2, J9.3, LEsp32.9
G26: LEsp32.10, R5.2, R8.1, R13.2
G27: LEsp32.11, R7.2, R15.2, R17.1
G32: LEsp32.7, R4.2, R6.1
G33: LEsp32.8, R11.2, R12.1
G34: J10.3, LEsp32.5
G35: LEsp32.6
GND: C1.2, C2.2, C3.2, C4.2, C5.2, C6.2, C7.2, C8.2, C9.2, D3.1 (-), D9.2 (A), D10.2 (A), J1.3, J3.2, J3.4, J4.3, J5.2, J7.2, J8.2, J9.2, J10.2, J11.2, J12.3, J13.2, J14.2, J15.2, J16.2, J19.2, J20.2, J21.8, J22.6, LEsp32.14, Q1.3 (E), Q2.3 (E), Q3.3 (E), Q4.3 (E), R6.2, R12.2, R13.1, R15.1, R16.1, R19.2, Resp32.1, Resp32.7, SW1.2
unnamed: D1.1 (K), F1.2
unnamed: D2.2 (A), J6.2, Q1.1 (C)
unnamed: D9.1 (K), J11.1, K4.3
unnamed: C7.1, D10.1 (K), J16.1, K6.3
unnamed: D11.2 (A), J15.1
unnamed: D11.1 (K), F1.1, J13PSW1.2, J14.1, R21.1
unnamed: D12.2 (A), J1.2, K4.2
unnamed: D13.2 (A), J12.2, K6.2
unnamed: D14.2 (A), J4.2, K5.2
unnamed: F2.1, K5.1
unnamed: J1.1, Q2.1 (C)
unnamed: J4.1, Q4.1 (C)
unnamed: J12.1, Q3.1 (C)
unnamed: J17.1, K5.3
unnamed: J17.2, J18.1
unnamed: F2.2, J18.2
unnamed: J21.1, R5.1
unnamed: J21.2, R7.1
unnamed: J21.3, R9.1
unnamed: J21.4, R10.1
unnamed: J21.5, R20.1
unnamed: J21.6, R3.1
unnamed: J21.7, R2.1
unnamed: Q1.2 (B), R1.2
unnamed: Q2.2 (B), R8.2
unnamed: Q3.2 (B), R17.2
unnamed: Q4.2 (B), R18.2
R12V+: D1.2 (A), D3.3 (+)
RX: Resp32.5
SD0: Resp32.18
SD1: Resp32.17
SD2: LEsp32.16
SD3: LEsp32.17
SM: LEsp32.4
SP: LEsp32.3, R19.1, R21.2
TX: Resp32.4
Turbidity_Signal: J8.3, R11.1
pH_Signal: J7.3, R4.1

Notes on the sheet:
RESET
pH Sensor (5v)
Heater Power Indicators
Power Filtering & Decoupling
Heater Control (240V)
Automated Fish Feeder (5v)
Turbidity Sensor (5v)
FAN Power Indicators
Auxiliary Fan Header (12v)
Main Power Input & Polarity Protection (5A)
Automated Fish Feeder Indicators
Stress-free ARGB Lighting (5v)
Solar Panel Input
BMS & Battery Level Monitor
Relay Pull-down
Cooling Fan Control (12v)
LCD Display(16*2) (5v)
Sachin Rathnayaka(WRSCN)
Operation Mode Selector (Auto (ON/OFF) / Manual ON / Emergency OFF)
Status & Power Indicators (LED)
5v Power Indicators
DC-DC step-down power module (12v - 5v)
Buzzer Alert (5v)
TDS Sensor (3.3v)
Water Pump (12v)
POWER_IN(12v)
Wi-fi Connect Indicators
DS18B20 Temperature Sensor (3.3v)
Real-Time Clock (RTC) DS3231 (3.3v)
12v Power Indicators
Pump Power Indicators
ESP32 Microcontroller Base
Reset Button & Boot Pull-ups

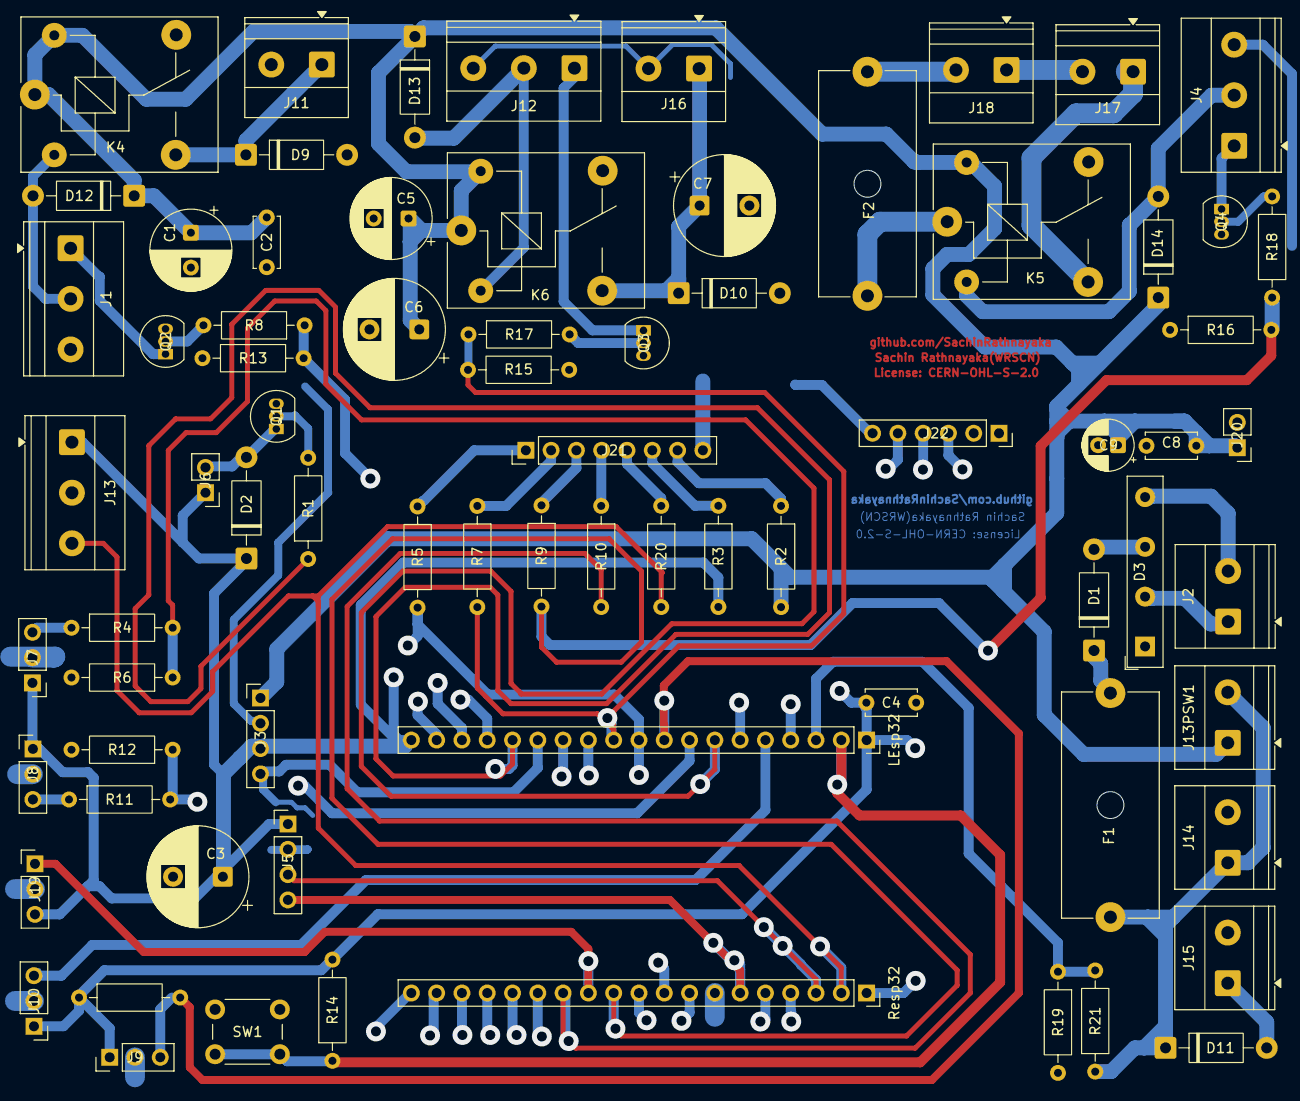
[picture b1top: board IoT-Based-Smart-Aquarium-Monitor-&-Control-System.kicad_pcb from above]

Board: 2 copper layers, 75 parts (0 on the bottom side), 51 nets.

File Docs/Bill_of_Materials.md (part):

# 📋 Bill of Materials (BOM)

**Project:** IoT-Based Smart Aquarium Monitor & Control System  
**Designed by:** Sachin Rathnayaka (WRSCN)  
**Institution:** Sri Lanka Institute of Information Technology (SLIIT)  
**Module:** Fundamentals of Computing (IT1140) — Y1S1  
**Schematic Rev:** 1.0  
**EDA Tool:** KiCad 10.0.3  
**License:** CERN-OHL-S-2.0  
**Repository:** [github.com/SachinRathnayaka/Smart-Aquarium-Monitor-Control-System](https://github.com/SachinRathnayaka/Smart-Aquarium-Monitor-C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  

---

> **Summary:** 41 line items — **74 total components**

> ⚠️ **Safety Warning:** This board includes 240 V AC mains wiring (J17, J18, K5 relay). All high-voltage sections must be handled by a qualified person. Use appropriate insulation, sleeving, and creepage clearances.

---

## 🧠 Microcontrollers  *(×1 total)*

| Reference | Qty | Description | Value / Specs | Package | Notes | Datasheet |
|-----------|-----|-------------|---------------|---------|-------|-----------|
| `LEsp32, Resp32` | 1 | ESP32 Development Board (38-pin) | ESP32-WROOM-32 / ESP32-DevKitC | DIP-38 / Module (fits 2× 1×19 female pin socket rows) | Dual-core 240 MHz, Wi-Fi + BT. Two 19-pin female socket rows on PCB. | [link](https://www.espressif.com/sites/default/files/documentation/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 |

## 🔧 Transistors  *(×4 total)*

| Reference | Qty | Description | Value / Specs | Package | Notes | Datasheet |
|-----------|-----|-------------|---------------|---------|-------|-----------|
| `Q1, Q2, Q3, Q4` | 4 | NPN General-Purpose Transistor | BC547 — 45 V, 100 mA | TO-92 Inline | Relay driver stages; Q1=heater relay, Q2=pump relay, Q3=feeder relay, Q4=fan relay. | [link](https://www.onsemi.com/pub/Collateral/BC550-D.pdf) |

## ⚡ Diodes  *(×9 total)*

| Reference | Qty | Description | Value / Specs | Package | Notes | Datasheet |
|-----------|-----|-------------|---------------|---------|-------|-----------|
| `D1, D9, D10, D11` | 4 | Schottky Rectifier Diode | SR560 — 60 V, 5 A | DO-41 (SOD81) P10.16mm Horizontal | Flyback / freewheeling diodes across relay coils & motor loads. | [link](http://www.vishay.com/docs/88503/1n4001.pdf) |
| `D2, D12, D13, D14` | 4 | General-Purpose Rectifier Diode | 1N4007 — 1000 V, 1 A | DO-41 (SOD81) P10.16mm Horizontal | Reverse-polarity protection & flyback suppression. | [link](http://www.vishay.com/docs/88503/1n4001.pdf) |
| `D3` | 1 | Bridge Rectifier Module | RS505 — 50 V PIV, 5 A | Diode Bridge 19.0×3.5×10.0mm P5.0mm | Full-wave bridge for AC→DC conversion on main power input. | [link](https://diotec.com/tl_files/diotec/files/pdf/datasheets/b40c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 |

## 🔋 Capacitors  *(×9 total)*

| Reference | Qty | Description | Value / Specs | Package | Notes | Datasheet |
|-----------|-----|-------------|---------------|---------|-------|-----------|
| `C1, C5` | 2 | Ceramic Disc Capacitor | 100 nF (0.1 µF) — 50 V | C Disc D5.0mm W2.5mm P5.00mm | Bypass / decoupling on power rails. | — |
| `C4, C8` | 2 | Ceramic Disc Capacitor | 100 nF (0.1 µF) — 50 V | C Disc D5.0mm W2.5mm P5.00mm | High-frequency decoupling near relay driver circuits. | — |
| `C2` | 1 | Electrolytic Capacitor (Polarized) | 470 µF — 25 V | CP Radial D8.0mm P3.50mm | Bulk filtering on regulated supply output. | — |
| `C3, C6, C7` | 3 | Electrolytic Capacitor (Polarized) | 1000 µF — 25 V | CP Radial D10.0mm P5.00mm | Main bulk filtering on 12 V and 5 V power rails. | — |
| `C9` | 1 | Electrolytic Capacitor (Polarized) | 10 µF — 25 V | CP Radial D5.0mm P2.00mm | Decoupling / soft-start capacitor. | — |

## 〰️ Resistors  *(×22 total)*

| Reference | Qty | Description | Value / Specs | Package | Notes | Datasheet |
|-----------|-----|-------------|---------------|---------|-------|-----------|
| `R5, R7, R9, R10, R20` | 5 | Carbon Film Resistor | 330 Ω — ¼ W, 5% | R Axial DIN0207 L6.3mm D2.5mm P10.16mm Horizontal | Current-limiting resistors for status / indicator LEDs. | — |
| `R3` | 1 | Carbon Film Resistor | 470 Ω — ¼ W, 5% | R Axial DIN0207 L6.3mm D2.5mm P10.16mm Horizontal | Base resistor / LED current limit. | — |
| `R1, R4, R8, R11, R17, R18` | 6 | Carbon Film Resistor | 1 kΩ — ¼ W, 5% | R Axial DIN0207 L6.3mm D2.5mm P10.16mm Horizontal | Transistor base resistors & pull-ups. (Schematic lists as '1Kom' and '1KOHM' — same value.) | — |
| `R6, R12` | 2 | Carbon Film Resistor | 2 kΩ — ¼ W, 5% | R Axial DIN0207 L6.3mm D2.5mm P10.16mm Horizontal | Voltage divider arms (sensor signal conditioning). | — |
| `R2` | 1 | Carbon Film Resistor | 2.2 kΩ — ¼ W, 5% | R Axial DIN0207 L6.3mm D2.5mm P10.16mm Horizontal | pH signal bias / divider. | — |
| `R13, R15, R16` | 3 | Carbon Film Resistor | 3.3 kΩ — ¼ W, 5% | R Axial DIN0207 L6.3mm D2.5mm P10.16mm Horizontal | I²C pull-up resistors (SDA/SCL lines to LCD & RTC). | — |
| `4.7kom1` | 1 | Carbon Film Resistor | 4.7 kΩ — ¼ W, 5% | R Axial DIN0207 L6.3mm D2.5mm P10.16mm Horizontal | DS18B20 temperature sensor 1-Wire pull-up resistor. | — |
| `R14, R19` | 2 | Carbon Film Resistor | 10 kΩ — ¼ W, 5% | R Axial DIN0207 L6.3mm D2.5mm P10.16mm Horizontal | EN/boot pull-up (R14) and BMS sense divider (R19). | — |
| `R21` | 1 | Carbon Film Resistor | 30 kΩ — ¼ W, 5% | R Axial DIN0207 L6.3mm D2.5mm P10.16mm Horizontal | Voltage divider upper arm (battery / solar level sense). | — |

## 🔌 Relays  *(×3 total)*

| Reference | Qty | Description | Value / Specs | Package | Notes | Datasheet |
|-----------|-----|-------------|---------------|---------|-------|-----------|
| `K4, K5, K6` | 3 | SPDT Relay — 5 V Coil | SANYOU SRD Series Form-C — 5 V coil, 10 A / 250 VAC contacts | Relay THT SPDT SANYOU SRD Form-C | K4 = Water pump, K5 = Heater (240 V), K6 = Auxiliary fan / cooling. | [link](http://www.sanyourelay.ca/public/products/pdf/SRD.pdf) |

## 🛡️ Fuses  *(×2 total)*

| Reference | Qty | Description | Value / Specs | Package | Notes | Datasheet |
|-----------|-----|-------------|---------------|---------|-------|-----------|
| `F1, F2` | 2 | Fuse Holder + Fuse — 5×20 mm | 5 A / 250 V slow-blow (or as per load; see notes) | Fuseholder Cylinder 5×20mm Schurter 0031.8201 Horizontal Open | F1 = Main DC input (12 V line). F2 = Secondary / sensor supply. Use appropriate ratings. | — |

## 🔘 Switchs  *(×1 total)*

| Reference | Qty | Description | Value / Specs | Package | Notes | Datasheet |
|-----------|-----|-------------|---------------|---------|-------|-----------|
| `SW1` | 1 | Momentary Push Button (Reset / Boot) | 6 mm × 6 mm tactile push button, SPST-NO | SW_PUSH_6mm THT | Reset button for ESP32. Also used as manual boot trigger (hold during power-on → download mode). | — |

## ⚙️ Power Modules  *(×1 total)*

| Reference | Qty | Description | Value / Specs | Package | Notes | Datasheet |
|-----------|-----|-------------|---------------|---------|-------|-----------|
| `J3` | 1 | DC-DC Buck Converter Module (12 V → 5 V) | LM2596 or MP1584 based — Input 12 V, Output 5 V / ≥2 A | 4-pin header 2.54 mm (mounts as sub-module) | Supplies 5 V rail for ESP32, relays, sensors & LCD. Pre-set output before installing. | — |

## 🔗 Connectors  *(×22 total)*

| Reference | Qty | Description | Value / Specs | Package | Notes | Datasheet |
|-----------|-----|-------------|---------------|---------|-------|-----------|
| `J1, J4, J12` | 3 | Screw Terminal Block — 3-pin | Pitch 5.08 mm, 15 A / 300 V | TerminalBlock Phoenix MKDS-1.5-3 P5.08mm Horizontal | J1 = Main power in/out bus, J4 = Water pump wiring, J12 = Auxiliary load wiring. | — |
| `J2, J11, J16` | 3 | DC Barrel Jack Terminal — 12 V Input | 2-pin screw terminal, 5.08 mm pitch | TerminalBlock Phoenix MKDS-1.5-2 P5.08mm Horizontal | 12 V DC supply connection points (J2 = main, J11 = backup/pump, J16 = fan/heatsink). | — |
| `J13PSW1` | 1 | 12 V Power Switch / Jack Terminal | 2-pin screw terminal, 5.08 mm pitch | TerminalBlock Phoenix MKDS-1.5-2 P5.08mm Horizontal | Operation mode selector input (Auto / Manual / Emergency OFF switch). | — |
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

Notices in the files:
README.md:
License: Multi-Licensed
